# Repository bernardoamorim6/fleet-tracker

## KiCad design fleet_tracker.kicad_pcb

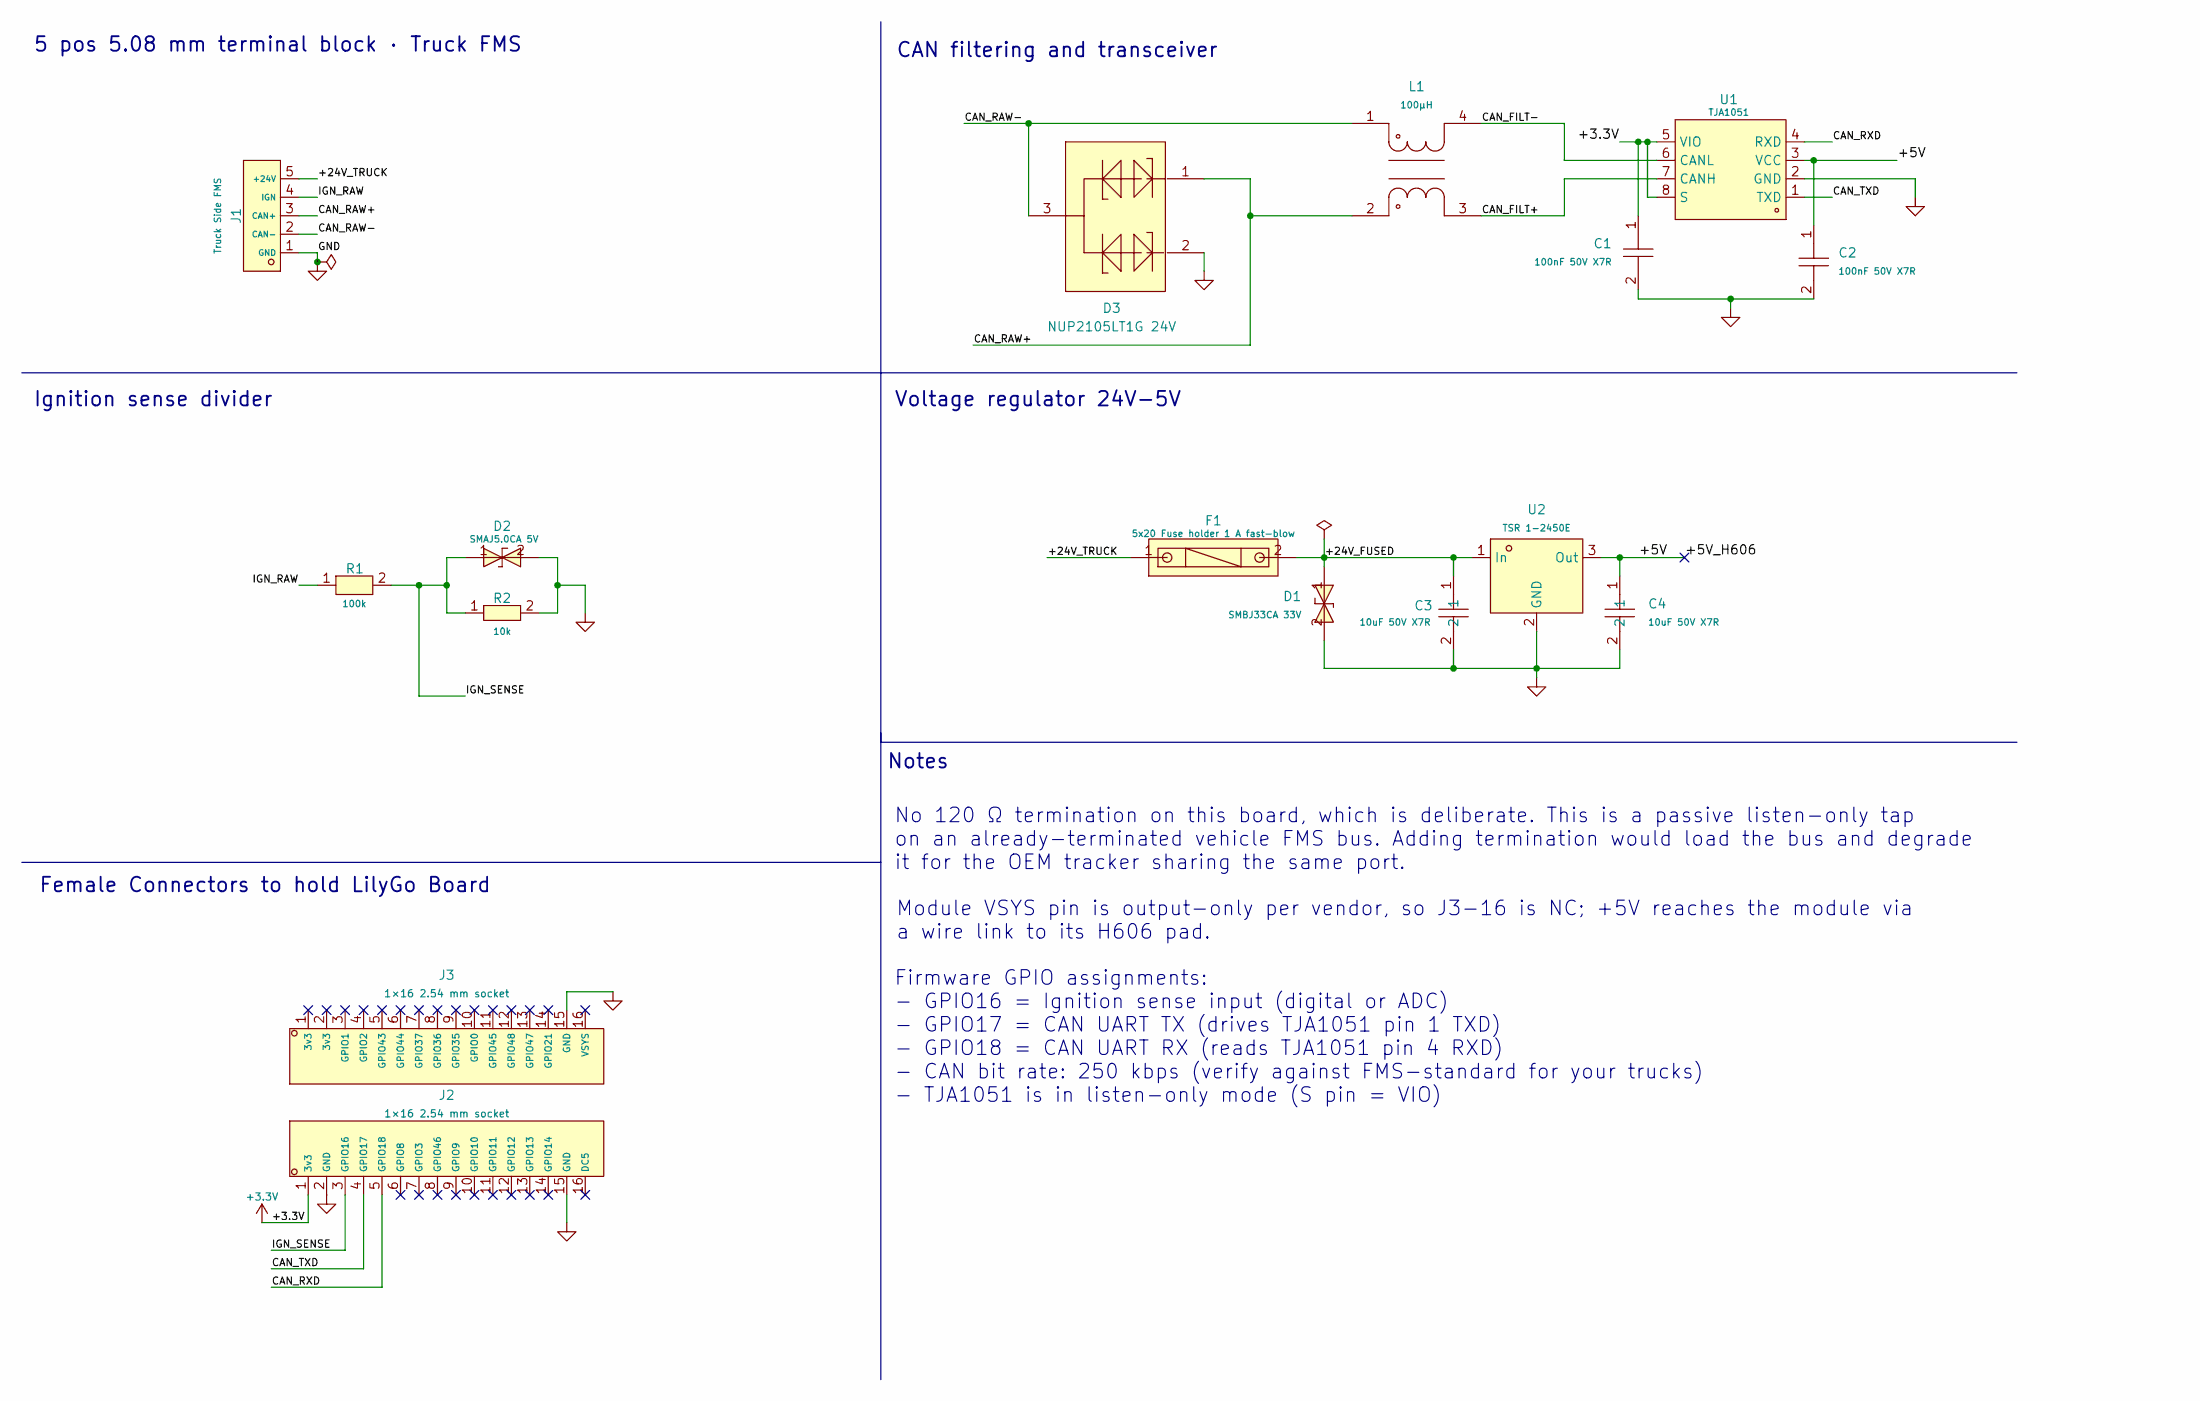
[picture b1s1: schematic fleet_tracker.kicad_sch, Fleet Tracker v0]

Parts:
C1, C2: 100nF 50V X7R; C0603; MPN CL10B104KB8NNNC; LCSC Part C1591
C3, C4: 10uF 50V X7R; C1206; MPN CL31B106KBHNNNE; LCSC Part C89632
D1: SMBJ33CA 33V; SMB_L4.3-W3.6-LS5.4-BI; MPN SMBJ33CA; LCSC Part C78420
D2: SMAJ5.0CA 5V; SMA_L4.4-W2.6-LS5.0-BI; MPN SMAJ5.0CA; LCSC Part C10756
D3: NUP2105LT1G 24V; SOT-23-3_L2.9-W1.3-P1.90-LS2.4-BL-2; MPN NUP2105LT1G; LCSC Part C14486
F1: 5x20 Fuse holder 1 A fast-blow; FUSE-TH_L22.6-W9.0; MPN 5x20 BLX-A型 保险丝支架 XC-7; LCSC Part C3131
J1: Truck Side FMS; CONN-TH_5P-P5.08_DIBO_DB128V-5.08-5P-GN-S; MPN DB128V-5.08-5P-GN-S; LCSC Part C2927513
J2, J3: 1×16 2.54 mm socket; HDR-TH_16P-P2.54-V-F-1; MPN 2685Y-116CNG1SNA01; LCSC Part C350305
L1: 100µH; FILTER-SMD_4P-L4.5-W3.2-TL_ACT45B; MPN ACT45B-101-2P-TL003; LCSC Part C88056
R1: 100k; R0603; MPN HoAR0603-1/10W-100KR-1%-TCR25; LCSC Part C2912579
R2: 10k; R0603; MPN RC0603FR-0710KL; LCSC Part C98220
U1: TJA1051; SOIC-8_L4.9-W3.9-P1.27-LS6.0-BL; MPN TJA1051T/3/1J; LCSC Part C38695
U2: TSR 1-2450E; PWRM-TH_3P-L11.6-W7.5-P2.54_TSR1-2433E; MPN TSR 1-2450E; LCSC Part C5346721

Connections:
+3.3V: C1.1, J2.1 (3v3), U1.5 (VIO), U1.8 (S)
/+5V: C2.1, C4.1, U1.3 (VCC), U2.3 (Out); also elsewhere on the board
/+24V_FUSED: C3.1, D1.1, F1.2, U2.1 (In)
/+24V_TRUCK: F1.1, J1.5 (+24V)
/CAN_FILT+: L1.3, U1.7 (CANH)
/CAN_FILT-: L1.4, U1.6 (CANL)
/CAN_RAW+: D3.1, J1.3 (CAN+), L1.2
/CAN_RAW-: D3.3, J1.2 (CAN-), L1.1
/CAN_RXD: J2.5 (GPIO18), U1.4 (RXD)
/CAN_TXD: J2.4 (GPIO17), U1.1 (TXD)
/IGN_RAW: J1.4 (IGN), R1.1
/IGN_SENSE: D2.1 (K), J2.3 (GPIO16), R1.2, R2.1
GND: C1.2, C2.2, C3.2, C4.2, D1.2, D2.2 (A), D3.2, J1.1 (GND), J2.2 (GND), J2.15 (GND), J3.15 (GND), R2.2, U1.2 (GND), U2.2 (GND)

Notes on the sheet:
Female Connectors to hold LilyGo Board
No 120 Ω termination on this board, which is deliberate. This is a passive listen-only tap on an already-terminated vehicle FMS bus. Adding termination would load the bus and degrade it for the OEM tracker sharing the same port.
Firmware GPIO assignments: - GPIO16 = Ignition sense input (digital or ADC) - GPIO17 = CAN UART TX (drives TJA1051 pin 1 TXD) - GPIO18 = CAN UART RX (reads TJA1051 pin 4 RXD) - CAN bit rate: 250 kbps (verify against FMS-standard for your trucks) - TJA1051 is in listen-only mode (S pin = VIO)
Voltage regulator 24V-5V
Module VSYS pin is output-only per vendor, so J3-16 is NC; +5V reaches the module via a wire link to its H606 pad.
Notes
Ignition sense divider
5 pos 5.08 mm terminal block · Truck FMS
CAN filtering and transceiver

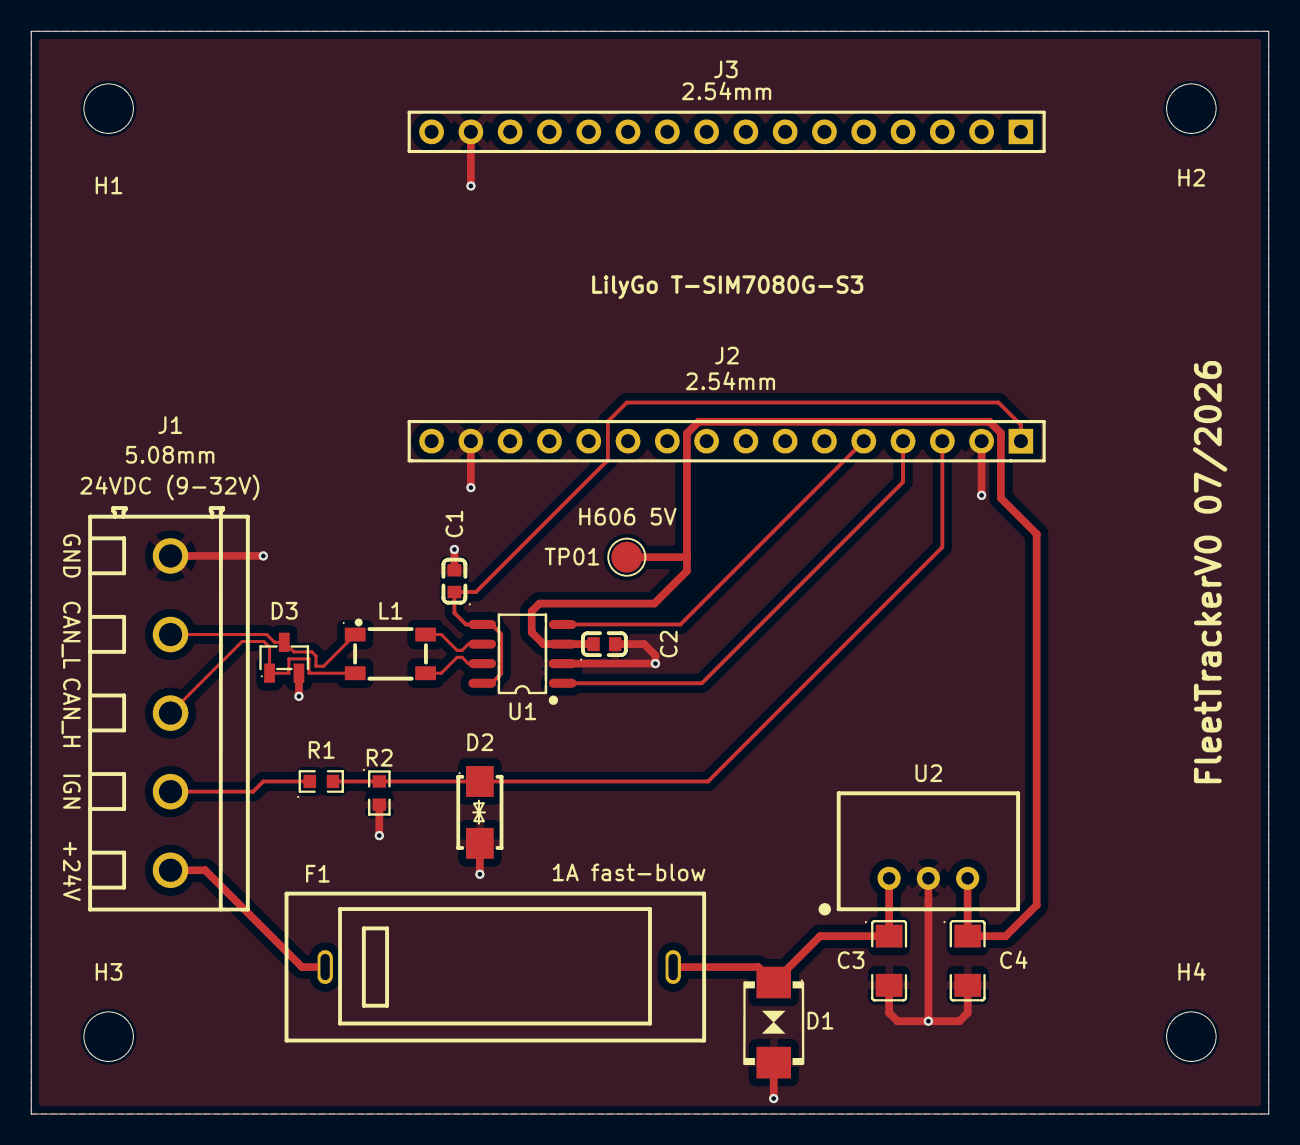
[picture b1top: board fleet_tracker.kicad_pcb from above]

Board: 2 copper layers, 80.0 x 70.0 mm, 21 parts (0 on the bottom side), 13 nets.

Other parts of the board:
H1, H2, H3, H4: MountingHole_3.2mm_M3
TP01: TestPoint_Pad_D2.0mm

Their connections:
/+5V: TP01.1; also elsewhere on the board
